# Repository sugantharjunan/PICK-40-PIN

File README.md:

# PIC 40-Pin Development Board – KiCad PCB Design

A compact and beginner-friendly **PIC 40-Pin Development Board** designed using **KiCad EDA** for schematic capture and PCB layout. This board is based on the **PIC16F877A microcontroller**, providing easy access to GPIO pins, communication peripherals, oscillator connections, and programming headers for embedded systems development.

The board is suitable for learning microcontrollers, embedded programming, interfacing sensors, and prototyping automation projects.

---

# Project Overview

This project demonstrates:

* PIC16F877A microcontroller minimum system design
* PCB design in KiCad
* Crystal oscillator interface
* GPIO breakout headers
* Power supply filtering
* Embedded development board layout
* 3D PCB visualization

---

# Features

* Supports PIC16F877A microcontroller
* 40-pin DIP socket support
* GPIO breakout headers
* Crystal oscillator support
* Reset and programming interface
* Compact PCB layout
* Beginner-friendly development board
* Designed using KiCad

---

# Software Used

* KiCad

Official Website: [KiCad Official Website](https://www.kicad.org?utm_source=chatgpt.com)

---

# Hardware Components

| Component          | Description               |
| ------------------ | ------------------------- |
| PIC16F877A         | 8-bit PIC Microcontroller |
| Crystal Oscillator | Clock source              |
| Capacitors         | Oscillator stabilization  |
| Pin Headers        | GPIO breakout             |
| DIP Socket         | Microcontroller mounting  |
| Power Connector    | +5V Supply Input          |

---

# Project Structure

```bash id="4o6uxu"
PIC-40PIN-DEVELOPMENT-BOARD/
│
├── Schematic/
│   └── pic_40pin_board.kicad_sch
│
├── PCB/
│   └── pic_40pin_board.kicad_pcb
│
├── Gerber/
│   └── Manufacturing_Files
│
├── Images/
│   ├── PIC_40PIN_3D_FRONT.png
│   ├── PIC_40PIN_3D_BACK.png
│   ├── PIC_40PIN_PCB.png
│   └── PIC_40PIN_SCHEMATIC.png
│
└── README.md
```

---

# Circuit Description

The development board is built around the **PIC16F877A** microcontroller.

The design includes:

* Crystal oscillator circuit
* Power supply filtering capacitors
* GPIO breakout headers
* Programming and communication connections
* Stable clock generation for microcontroller operation

---

# Working Principle

1. +5V supply powers the microcontroller.
2. Crystal oscillator generates clock pulses.
3. PIC16F877A executes programmed instructions.
4. GPIO headers allow interfacing external modules.
5. Peripheral interfaces support embedded applications.

---

# PCB Design

The PCB was designed with:

* Clean signal routing
* Organized GPIO breakout layout
* Through-hole component placement
* Compact board structure
* Easy soldering access
* Stable power and clock routing

---

# Pin Configuration

The board exposes:

* PORTA
* PORTB
* PORTC
* PORTD
* PORTE
* MCLR
* Power Pins
* Oscillator Pins

for external interfacing.

---

# Electrical Specifications

| Parameter       | Value            |
| --------------- | ---------------- |
| Microcontroller | PIC16F877A       |
| Supply Voltage  | +5V DC           |
| Oscillator      | External Crystal |
| GPIO Support    | Yes              |
| PCB Tool        | KiCad            |

---

# Applications

* Embedded Systems Development
* PIC Programming Practice
* Sensor Interfacing
* Robotics
* Industrial Automation
* IoT Prototyping
* Academic Projects
---
# Development Notes

This board can be used with:

* MPLAB X IDE
* PICkit Programmer
* Embedded C
* MikroC
* XC8 Compiler

---

# Future Improvements

* Add onboard regulator
* Add USB programming support
* Add UART interface
* Add LCD connector
* Add onboard debugging LEDs

This project is open-source and available under the MIT License.

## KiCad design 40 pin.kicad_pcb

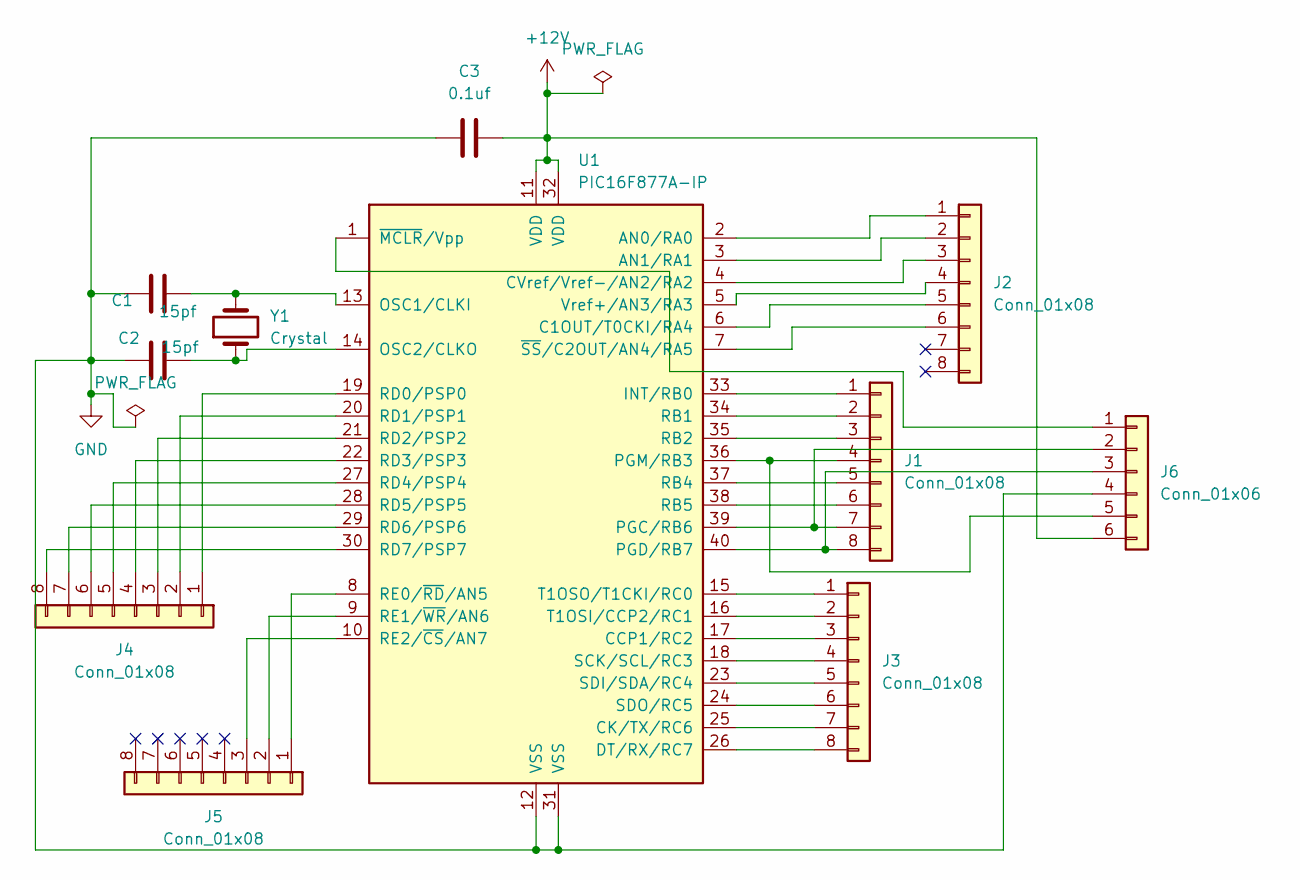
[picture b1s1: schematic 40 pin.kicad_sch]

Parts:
C1, C2: 15pf; CP_Radial_D4.0mm_P1.50mm
C3: 0.1uf; CP_Radial_D4.0mm_P1.50mm
J1, J2, J3, J4, J5: Conn_01x08; PinHeader_1x08_P2.54mm_Vertical
J6: Conn_01x06; PinHeader_1x06_P2.54mm_Vertical
U1: PIC16F877A-IP; DIP-40_W15.24mm
Y1: Crystal; Crystal_HC49-U_Vertical

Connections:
+12V: C3.2, J6.6, U1.11 (VDD), U1.32 (VDD)
GND: C1.1, C2.2, C3.1, J6.4, U1.12 (VSS), U1.31 (VSS)
unnamed: J1.1, U1.33 (INT/RB0)
unnamed: J1.2, U1.34 (RB1)
unnamed: J1.3, U1.35 (RB2)
unnamed: J1.4, J6.5, U1.36 (PGM/RB3)
unnamed: J1.5, U1.37 (RB4)
unnamed: J1.6, U1.38 (RB5)
unnamed: J1.7, J6.2, U1.39 (PGC/RB6)
unnamed: J1.8, J6.3, U1.40 (PGD/RB7)
unnamed: J2.1, U1.2 (AN0/RA0)
unnamed: J2.2, U1.3 (AN1/RA1)
unnamed: J2.3, U1.4 (CVref/Vref-/AN2/RA2)
unnamed: J2.4, U1.5 (Vref+/AN3/RA3)
unnamed: J2.5, U1.6 (C1OUT/T0CKI/RA4)
unnamed: J2.6, U1.7 (~SS/C2OUT/AN4/RA5)
unnamed: J3.1, U1.15 (T1OSO/T1CKI/RC0)
unnamed: J3.2, U1.16 (T1OSI/CCP2/RC1)
unnamed: J3.3, U1.17 (CCP1/RC2)
unnamed: J3.4, U1.18 (SCK/SCL/RC3)
unnamed: J3.5, U1.23 (SDI/SDA/RC4)
unnamed: J3.6, U1.24 (SDO/RC5)
unnamed: J3.7, U1.25 (CK/TX/RC6)
unnamed: J3.8, U1.26 (DT/RX/RC7)
unnamed: J4.1, U1.19 (RD0/PSP0)
unnamed: J4.2, U1.20 (RD1/PSP1)
unnamed: J4.3, U1.21 (RD2/PSP2)
unnamed: J4.4, U1.22 (RD3/PSP3)
unnamed: J4.5, U1.27 (RD4/PSP4)
unnamed: J4.6, U1.28 (RD5/PSP5)
unnamed: J4.7, U1.29 (RD6/PSP6)
unnamed: J4.8, U1.30 (RD7/PSP7)
unnamed: J5.1, U1.8 (RE0/~RD/AN5)
unnamed: J5.2, U1.9 (RE1/~WR/AN6)
unnamed: J5.3, U1.10 (RE2/~CS/AN7)
unnamed: J6.1, U1.1 (~MCLR/Vpp)
unnamed: C1.2, U1.13 (OSC1/CLKI), Y1.2
unnamed: C2.1, U1.14 (OSC2/CLKO), Y1.1

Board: 2 copper layers, 11 parts (0 on the bottom side), 38 nets, no tracks yet.
